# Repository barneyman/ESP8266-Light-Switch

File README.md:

# ESP8266-Light-Switch

I now use Home Assistant to drive this, it's also changed to support other devices - it's on my list to update this readme

When it starts it has no AP credentials to join your LAN, so offers up its own AP, which you can surf to
(192.168.4.1 by default) and give it credentials - it saves those in flash and will use them every time it reboots

It is possible to OTA update the firmware, and web pages

it was written using the Arduino extension for VSCode, but should compile perfectly well in other Arduino aware IDEs

It talks to [Home Assistant](https://github.com/home-assistant/core) using my [custom component](https://github.com/barneyman/custom_components) - there is also an update [Addon](https://github.com/barneyman/updateServerAddOnHA)

Example six-way switch

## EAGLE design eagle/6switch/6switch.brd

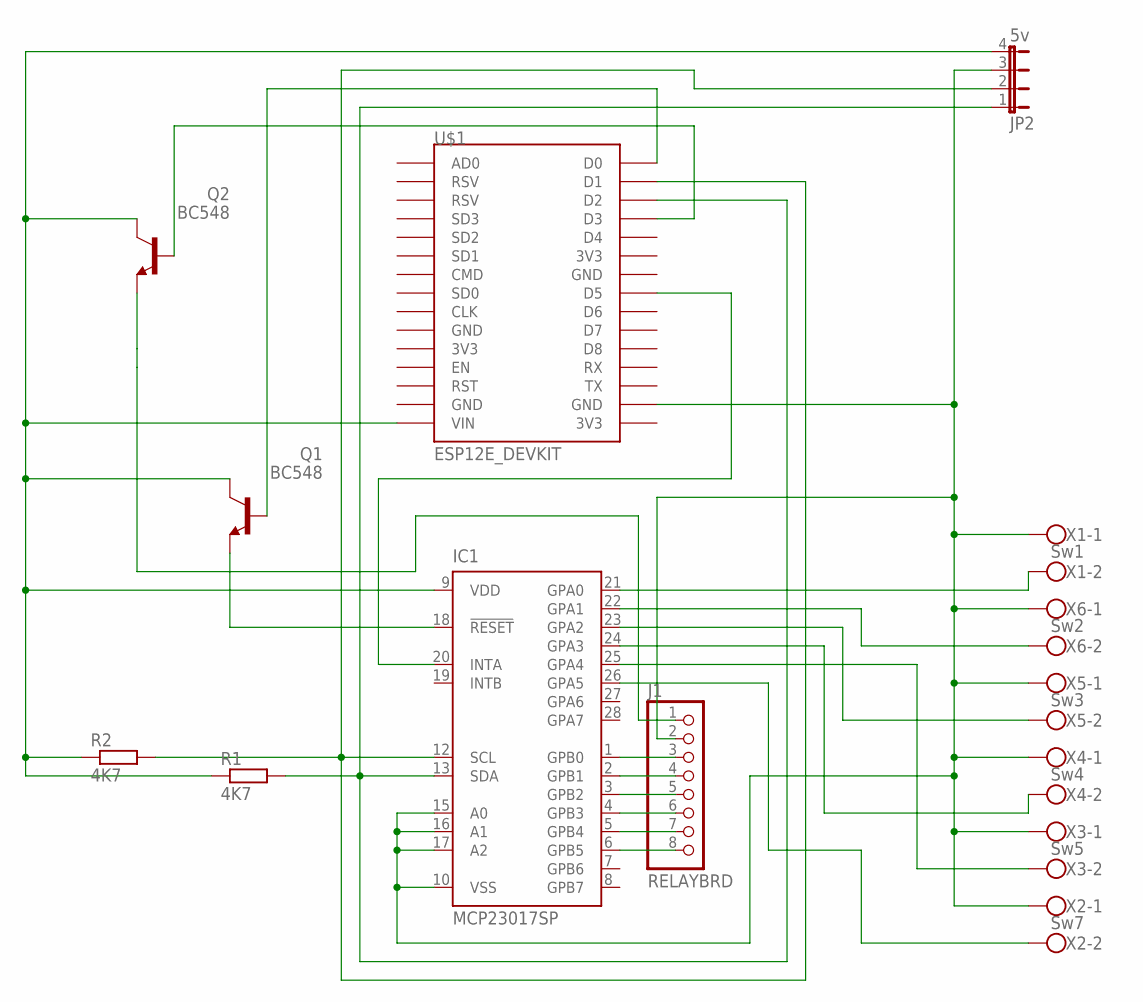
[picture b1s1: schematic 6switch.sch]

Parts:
IC1: MCP23017SP; DIL28-3
J1: RELAYBRD; 1X08
JP2: 5v; JP4
Q1, Q2: BC548; TO92-EBC
R1, R2: 4K7; 0207/10
U$1: ESP12E_DEVKIT
X1: Sw1; W237-102
X2: Sw7; W237-102
X3: Sw5; W237-102
X4: Sw4; W237-102
X5: Sw3; W237-102
X6: Sw2; W237-102

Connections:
GND: IC1.10 (VSS), IC1.15 (A0), IC1.16 (A1), IC1.17 (A2), J1.2, JP2.3, U$1.GND@3 (GND), X1.1, X2.1, X3.1, X4.1, X5.1, X6.1
unnamed: Q1.B, U$1.D0
unnamed: IC1.18 (!RESET), Q1.E
unnamed: J1.1, Q2.E
unnamed: Q2.B, U$1.D3
unnamed: IC1.22 (GPA1), X6.2
unnamed: IC1.1 (GPB0), J1.3
unnamed: IC1.20 (INTA), U$1.D5
unnamed: IC1.23 (GPA2), X5.2
unnamed: IC1.24 (GPA3), X4.2
unnamed: IC1.21 (GPA0), X1.2
unnamed: IC1.2 (GPB1), J1.4
unnamed: IC1.3 (GPB2), J1.5
unnamed: IC1.4 (GPB3), J1.6
unnamed: IC1.5 (GPB4), J1.7
unnamed: IC1.6 (GPB5), J1.8
unnamed: IC1.25 (GPA4), X3.2
unnamed: IC1.26 (GPA5), X2.2
SCL: IC1.12 (SCL), JP2.2, R2.2, U$1.D1
SDA: IC1.13 (SDA), JP2.1, R1.2, U$1.D2
VCC: IC1.9 (VDD), JP2.4, Q1.C, Q2.C, R1.1, R2.1, U$1.VIN

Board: 2 copper layers, 14 parts (0 on the bottom side), 21 nets, no tracks yet.

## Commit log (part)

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2020-03-11 Builds on a clean arduino-cli now - next is to use a runner
2020-03-11 remove elf
2020-03-11 Create main.yml
    first workflow
2020-03-11 Update main.yml
    added submodules
2020-03-11 Update main.yml
    added tar / create release / upload asset
2020-03-11 Update main.yml
    bin and elf
2020-03-11 save wemos d1
2020-03-11 added matrix
2020-03-11 fixed
2020-03-11 fixed?
2020-03-11 i hate yaml
2020-03-11 yay for vscode extensions
2020-03-11 quotes
2020-03-11 remove generic for the moment
2020-03-11 prerelease
2020-03-11 pinning ESP core
2020-03-11 Update main.yml
    added edited
2020-03-11 Update main.yml
    kitchen sink
2020-03-11 Update main.yml
    ${GITHUB_REF}
2020-03-12 try changing ref
2020-03-12 github ref hate
2020-03-15 added LED to PIR
2020-03-15 remove 6switch
2020-03-21 changing the OTA method
2020-03-22 env vars naming
2020-03-22 beginning to understand
2020-03-22 getting cocky?
2020-03-22 braces
2020-03-22 spot draft / prelease
2020-03-22 remove body
2020-03-22 guessing
2020-03-22 release naming
2020-03-22 more
2020-03-22 run it off tag create now
2020-03-22 mkspiffs
2020-03-25 tring spiffs
2020-03-25 solve my problem first - then the 'copy' problem
    arduino-cli is not post-link copying because ... reasons
2020-03-25 naming hack
2020-03-25 added spiffs bin
2020-03-25 id for name
2020-03-25 turn cron off
2020-03-25 size
2020-03-26 changed mkspiffs
2020-03-26 re-order
2020-03-26 put spiffs cmd line in matrix
2020-03-26 removed matrix elements
2020-03-26 no cron
2020-03-26 will now compile generic
2020-03-26 added generic
2020-03-26 demunged
2020-03-26 go with tags
2020-03-26 added config schema
2020-03-27 rearranged into multiple jobs
2020-03-27 change asset upload name
2020-03-27 name fully qualified
2020-04-01 filename change
2020-04-18 changed asset names, friendly at the front
2020-04-18 draft status
    creates the release as a draft, uploads assets, then undrafts it
2020-04-18 Fixed ID
2020-04-18 pre-release
2020-04-18 quotes!
2020-04-19 runid on the spiffs file too
2020-04-19 filename corrected
2020-04-21 added defines and changed wemos spiffs size
2020-04-21 compiler.c.extra_flags
2020-04-22 changed ver of mkspiffs
    current esp8266 core uses 0.2.0
2020-04-22 no magic length
2020-04-22 changed memory size
2020-04-22 platform options
2020-04-22 removed :
2020-04-24 compiles for sonoff
2020-04-24 updatespiffs / updatebin works
2020-04-25 fixed command line defines
2020-04-25 fixed friendlyname, safeguards in loop()
2020-04-25 move vtables to iram
2020-04-26 successfully compilled for sonoff
2020-04-26 more options
2020-04-26 minify data
2020-04-26 added SonoffBasic
2020-04-27 pinned minify action
2020-04-27 remove minify
2020-05-07 fixed announce for sonoff
2020-05-08 honour... for mometary
2020-05-08 sonoff led is 1:1
2020-05-08 remove 10sec startup for production build
2020-05-08 renamed
2020-05-08 fixed sonoff led
2020-05-08 preserve state
2020-05-08 preserveState before update
2020-05-09 let ME reboot
2020-05-09 sonoff build info
2020-05-10 get pir working again
2020-05-10 html redesign
2020-05-10 home screen
2020-05-11 more html changes
2020-05-11 removed debug
2020-05-11 fixed sonoff boot led
2020-05-12 late fill peer info
2020-05-12 cruft
2020-05-12 added prerelease, made posts, posts
2020-05-13 setname
2020-05-13 minify
2020-05-13 colours
2020-05-13 pre-release, POST, set name
2020-05-14 update when off, reinstate button GET temporarily
2020-05-22 set logging
2020-05-22 changed log level
2020-05-23 logging options
2020-05-24 guard against nullptr
2020-05-24 Guard nullptr, createLogger, removed prettyprint, HTTP_POST
2020-05-24 reset base
2020-05-26 spot extra change too
2020-05-26 wizard for config
2020-05-26 html name changes
2020-05-27 fixed error page
2020-05-27 fixed multisensor display
2020-05-27 update asynch
2020-05-28 removed MQTT
2020-06-06 added d1
2020-06-07 mods for ESP32
2020-06-08 removed unused
2020-06-08 cruft, moved all vars into details, don't store static
2020-06-14 moved
2020-06-21 added esp32cam
2020-08-03 runtime config
2020-08-09 add/del devices works
2020-08-09 cleaned up
2020-08-09 compiles for esp32cam
2021-02-16 check count before create
2021-02-16 debug
2021-02-16 removed deprecated set-env
2021-02-16 rev'd arduino-cli
2021-02-16 arduino index update
2021-02-17 arduino-cli flags
2021-02-17 arduino-cli mandates ino name change
2021-02-17 removed lightswitch.ino
2021-02-17 outputdir here
2021-02-17 removed esp32
2021-02-17 fixed oktokit warning?
2021-02-18 prep for CI
2021-02-18 fixed conditions, probably
2021-02-18 conditionals
2021-02-18 added req.txt for pyserial, for esp
2021-02-18 retry esp32
2021-02-18 added changelisting
2021-02-18 minimal pckage.json
2021-02-18 remove changelog
2021-11-04 change hPA to hPa (for HA)
2021-11-24 build errors
2021-11-24 build fixes
2021-11-24 force esp32 ver
2021-11-24 latest v2
2021-11-25 complain if no devices
2021-11-25 rename hex files
2021-11-26 remove tarpit
2021-11-27 simplified platform
2021-12-24 how to make / upload images
2021-12-24 build msgs
2021-12-24 debug bug
2021-12-24 logging
2021-12-24 bug and log
2021-12-24 fixewd wifi population
2021-12-24 linted, and changed a fn name
2021-12-24 fn renames
2021-12-25 some renames, refresh issues resolved
2021-12-25 try1
2021-12-26 fixed joinwifi
2021-12-26 docs
2021-12-26 migrated to fetch
2021-12-26 bug fixes
2021-12-26 fixed logging bug
2021-12-26 ignore img
2021-12-27 esp32 compiles
2021-12-28 avoid update logic hole
2021-12-29 src changes
2021-12-29 burn sonoff
2021-12-29 pedantic
2022-01-05 update bugs
2022-01-05 more errs
2022-01-05 ignore .spiffs
2022-01-05 prod tweaks
2022-01-06 sonoff change
2022-01-12 vuejs PoC
2022-01-12 esp32cam spiffs details
2022-01-12 joinfg wifi in loop
2022-01-14 vuejs 80%
2022-01-14 cors
2022-01-15 bump
2022-01-15 build fix
2022-01-26 next-prev
2022-01-27 wizard fixes
2022-02-19 ico size
2022-02-20 remove CORS
2022-02-20 changes for default.htm
2022-02-20 docker spiffs creation
2022-02-20 gzip'd
2022-02-20 tidy up
2022-02-20 reference
2022-02-20 reference min
2022-02-20 clean
2022-02-20 exclude vuejs
2022-02-21 mkspiffs change and data.vue
2022-02-23 dhcp bug
2022-02-23 select load fix
2022-02-26 defaults
2022-02-26 OTA synchronous
2022-02-26 remove reboots
2022-02-26 change wifi in loop()
2022-02-26 cursor
2022-02-26 crlf fix
2022-02-26 camera img
2022-02-27 yield safe
2022-02-27 remove fakecameras
2022-02-27 remove lamda in lambda
2022-02-27 fixed sync send of binary
2022-02-27 sync webserver
2022-02-27 seems stable
2022-03-05 esp8266 3.0.2 / esp32 2.0.2
2022-03-05 remove malloc/free
2022-03-05 build fix, fix
2022-03-05 build fix, fix, fix
2022-04-12 heap corruption bug
2022-04-12 more debug
2022-04-13 rescan wifi
2022-04-13 formatting
2022-04-13 serialise camera access
2022-04-13 bump for new boards
2022-04-13 bump for latest websrv
2022-04-19 sonoff changes
2022-04-20 SPIFFS - minimise space
2022-04-20 wemos def change
2022-04-20 reduce SPIFFS
2022-04-20 limit refreshes
2022-04-20 wifi scan button
2022-04-20 esp32 build fix
2022-04-22 mdns servicetexts
2022-04-22 esp32 fix
2022-04-22 do updates async
2022-04-22 gzip web
2022-04-22 stabilist OTA FS
2022-04-23 301 for root
2022-04-23 gz fun
2022-04-23 add ver to mdns txt
2022-04-24 SPIFFS state
2022-04-24 change version (upgrade testing)
2022-04-24 fixed text
2022-04-24 change debug, wait between OTA
2022-04-24 verbosity
2022-04-26 moved data.vue
2022-04-26 moved data.vue to data
2022-05-05 fix 'exception 0 in httpclient.end()'
2022-07-25 underscores aren't DNS friendly
2022-07-25 pin arduino-cli to 0.22.0
2022-07-31 changed to sending events
2022-07-31 doco
2022-08-14 mkspiffs imager
2022-11-25 added PR and print context
2022-11-25 fix python ref
2022-11-27 fixate ubuntu at 2004
2022-11-27 git version
2022-11-28 Fix py (#4)
    * fixate ubuntu at 2004
    * git version
2022-12-28 try ending spiffss
2023-01-06 begin
2023-03-11 LUX -> lx
2023-03-11 wemos are only sensors
2023-04-07 handle spiffs better
2023-04-17 update subs
2023-04-17 produce artifacts
2023-04-17 upstream fixes
2023-04-17 devcontainer
2023-04-17 makes
2023-04-17 ignore map
2023-04-17 install spiffs
2023-04-17 stop builds on branch
2023-04-17 fix esp32cam_spiffs
2023-04-20 burn bin and spiffs
2023-04-20 dev build
2023-04-20 slower serial
2023-04-22 serial 38400
2023-04-22 CRLF
2023-04-22 mdns more often in devbuild
2023-04-22 restart mdns
2023-04-22 nightly
2023-04-22 name change
2023-04-22 better error
2023-04-22 semver
2023-04-22 remove delay
2023-04-22 fix names
2023-04-22 sonoff
2023-04-22 bump subs
2023-04-23 bump wifi
2023-04-23 interactive
2023-04-23 consistent dirs
2023-04-23 use installed tools
2023-04-24 codespaces variant
2023-04-24 cleanup & versioning
2023-04-24 use toolchain mkspiffs
2023-04-24 fix artifact upload name
2023-04-24 errant $
2023-04-24 fix dir
2023-04-24 cleanup
2023-04-24 move version
2023-04-24 simplify release assets
2023-04-24 broke the `needs`
2023-04-24 versioning
2023-04-24 checkout
2023-04-24 yaml!
2023-04-24 fixes
2023-04-24 nearly there
2023-04-24 id not name!
2023-04-24 test ver bump
2023-04-24 abandoning versioning
2023-04-24 spot tagging
2023-04-24 bools?!
2023-04-24 don't quote
2023-04-24 fix path
2023-04-24 working; cleanup
2023-04-30 fix friendly name
2023-04-30 bump ver
2023-04-30 dev ver num
2023-04-30 might use this anyway
2023-04-30 fix dirs
2023-05-01 cleaned update up
2023-05-01 fixed ver
2024-10-15 helpers
2024-10-15 fixes for pythonh
2024-10-15 change default logging
2024-10-15 fix checkout
2024-10-15 remove espcam
2024-10-15 update actions
2024-10-29 simplify updates, single URL
2024-10-29 don't leak auth
2024-10-29 switch default br to main
2024-12-10 pull out on/off
2025-04-07 linux change
2025-04-07 add esp32 wroom
2025-04-07 seperated ESP32CAM and ESP32
2025-04-07 esp32-wroom can be written
2025-04-09 fixes for esp32cam
2025-04-09 IRAM_ATTR fix
2025-04-09 fix leaking file handle
2025-04-09 fix for ESP32 webserver
2025-04-09 more esp32/esp8266 diffs
2025-04-10 subs
2025-04-14 AsyncWeb server updates
2025-04-14 ESP32 fixes
2025-04-14 remove define
2025-04-14 oops
2025-04-27 up to date
